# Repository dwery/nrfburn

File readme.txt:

This hardware/software package allows full access to the flash area of the Nordic nRF24LU1+ and nRF24LE1 microcontrollers.

The programmer is based on an Atmel ATmega AVR which handles the SPI communication and access to the flash area of the Nordic nRF MCUs. It can erase, write and read the MainBlock and InfoBlock of the nRF flash.

NOTE: Flash read access is only possible if it has been allowed by the nRF InfoPage configuration.

nrfburn can be used to access the flash of "bricked" nRF24LU1+ (both versions: F16 and F32) or nRF24LE1 MCUs. You can reprogram the bootloader or write any other HEX file into the flash area.

Tha programmer hardware is built around an Atmel ATmega88p microcontroller, but ATmega168p or ATmega328p can be used as well. The programmer firmware uses V-USB for communication with the PC. The PCB has breakout footprints compatibile with the SparkFun nRF24LU1+ breakout board, and a generic nRF24LU1+ dongle. This means that you can just plug these breakouts into the programmer to flash the nRF MCU.

Project modules:

AVR circut - Eagle CAD files for the AVR programmer circuit.

firmware - The AVR programmer firmware. It parses requests received from USB and executes SPI commands to access the nRF flash.

nrfburn - PC software which sends commands to the AVR programmer. Written in C++, it is cross-platform and can be compiled with gcc for Linux or Windows (MinGW).

nrfburn is still under active development, and parts of it are not working. It has not yet been tested with nRF24LE1 and problems are expected.

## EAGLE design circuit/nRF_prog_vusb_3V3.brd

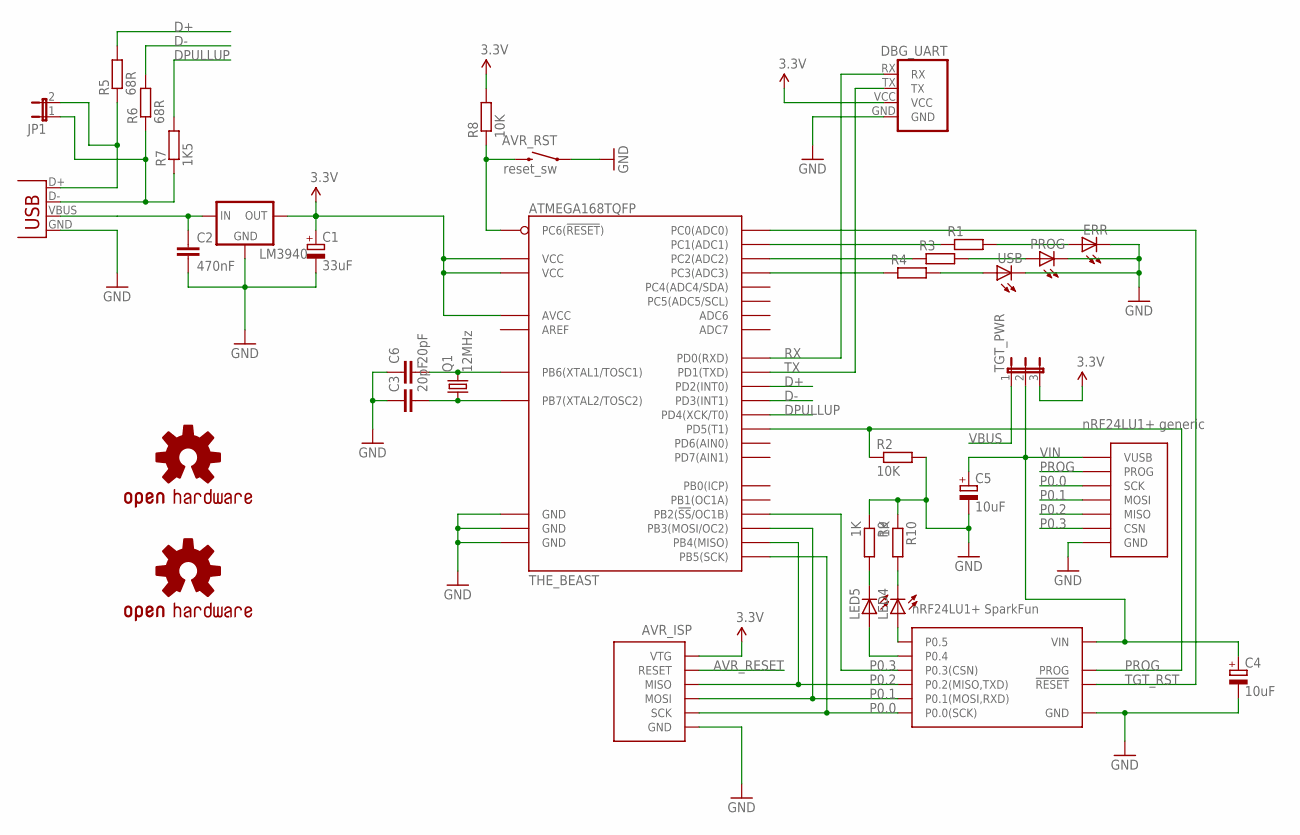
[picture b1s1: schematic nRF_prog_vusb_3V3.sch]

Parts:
AVR_ISP: AVR-ISP-6SMALL_FP; AVR-ISP-6-SMALL-FP
AVR_RST: reset_sw; TACTILE_SWITCH_SMD
C1: 33uF; SMC_B
C2: 470nF; C0805K
C3, C6: 20pF; C0805
C4, C5: 10uF; SMC_B
DBG_UART: UART_PORT
ERR: LEDCHIPLED_0805; CHIPLED_0805
JP1: JP1E; JP1
LED4, LED5: LEDCHIPLED_0805; CHIPLED_0805
LM3940: LM3940; SOT223
LU1+_GENERIC: NRF24LU1P_GENERIC
LU1+_SPARKFUN: NRF24LU1P_SPARKFUN_BREAKOUT; NRF24LU+_SPARKFUN_BREAKOUT
PROG: LEDCHIPLED_0805; CHIPLED_0805
Q1: 12MHz; QUARTZ
R1, R3, R4: R-EU_M0805; M0805
R2, R8: 10K; M0805
R5, R6: 68R; M0805
R7: 1K5; M0805
R9, R10: 1K; M0805
TGT_PWR: JP2E; JP2
THE_BEAST: ATMEGA168TQFP; TQFP32-08
U$1: OSHW-LOGOM; OSHW-LOGO-M
U$2: OSHW-LOGOL; OSHW-LOGO-L
USB: LEDCHIPLED_0805; CHIPLED_0805
USB-B: USBPTH; USB-B-PTH

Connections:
3.3V: AVR_ISP.VCC (VTG), C1.+, DBG_UART.VCC, LM3940.3 (OUT), R8.2, TGT_PWR.3, THE_BEAST.4 (VCC), THE_BEAST.6 (VCC), THE_BEAST.18 (AVCC)
AVR_RESET: AVR_ISP.RESET, AVR_RST.3 (2), R8.1, THE_BEAST.29 (PC6(!RESET!))
D+: R5.2, THE_BEAST.32 (PD2(INT0))
D-: R6.2, THE_BEAST.1 (PD3(INT1))
DPULLUP: R7.2, THE_BEAST.2 (PD4(XCK/T0))
GND: AVR_ISP.GND, AVR_RST.1, C1.-, C2.2, C3.1, C4.-, C5.-, C6.1, DBG_UART.GND, ERR.C, LM3940.2 (GND), LM3940.4 (GND), LU1+_GENERIC.GND, LU1+_SPARKFUN.GND, PROG.C, R2.2, R9.1, R10.1, THE_BEAST.3 (GND), THE_BEAST.5 (GND), THE_BEAST.21 (GND), USB.C, USB-B.GND
unnamed: LED4.A, LU1+_SPARKFUN.P0.5
unnamed: LED5.A, LU1+_SPARKFUN.P0.4
unnamed: LED4.C, R10.2
unnamed: LED5.C, R9.2
unnamed: R4.1, THE_BEAST.26 (PC3(ADC3))
unnamed: R3.1, THE_BEAST.25 (PC2(ADC2))
unnamed: R1.1, THE_BEAST.24 (PC1(ADC1))
unnamed: R4.2, USB.A
unnamed: PROG.A, R3.2
unnamed: ERR.A, R1.2
unnamed: C6.2, Q1.2, THE_BEAST.7 (PB6(XTAL1/TOSC1))
unnamed: C3.2, Q1.1, THE_BEAST.8 (PB7(XTAL2/TOSC2))
P0.0: AVR_ISP.SCK, LU1+_GENERIC.SCK, LU1+_SPARKFUN.P0.0 (P0.0(SCK)), THE_BEAST.17 (PB5(SCK))
P0.1: AVR_ISP.MOSI, LU1+_GENERIC.MOSI, LU1+_SPARKFUN.P0.1 (P0.1(MOSI,RXD)), THE_BEAST.15 (PB3(MOSI/OC2))
P0.2: AVR_ISP.MISO, LU1+_GENERIC.MISO, LU1+_SPARKFUN.P0.2 (P0.2(MISO,TXD)), THE_BEAST.16 (PB4(MISO))
P0.3: LU1+_GENERIC.CSN, LU1+_SPARKFUN.P0.3 (P0.3(CSN)), THE_BEAST.14 (PB2(!SS!/OC1B))
PROG: LU1+_GENERIC.PROG, LU1+_SPARKFUN.PROG, R2.1, THE_BEAST.9 (PD5(T1))
RX: DBG_UART.RX, THE_BEAST.30 (PD0(RXD))
TGT_RST: LU1+_SPARKFUN.RESET (!RESET!), THE_BEAST.23 (PC0(ADC0))
TX: DBG_UART.TX, THE_BEAST.31 (PD1(TXD))
USB_D+: JP1.2, R5.1, USB-B.D+
USB_D-: JP1.1, R6.1, R7.1, USB-B.D-
VBUS: C2.1, LM3940.1 (IN), TGT_PWR.1, USB-B.VBUS
VIN: C4.+, C5.+, LU1+_GENERIC.VUSB, LU1+_SPARKFUN.VIN, TGT_PWR.2

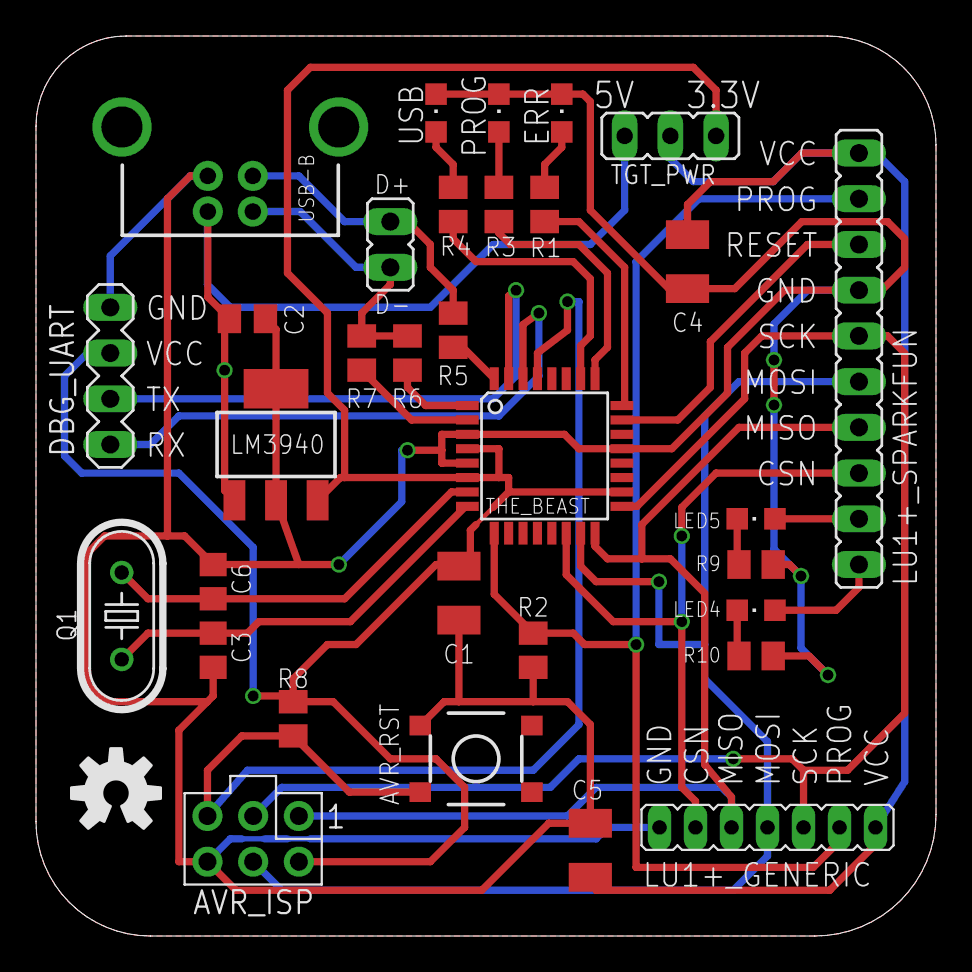
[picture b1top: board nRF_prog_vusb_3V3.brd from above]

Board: 2 copper layers, 50.0 x 50.0 mm, 34 parts (1 on the bottom side), 30 nets.

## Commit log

2013-12-23 added flash verification
2013-12-23 linux usb_dev_handle casts
2013-12-23 labels and messages fix
2013-12-29 New version works uses reset which hopefully fixes the problems with programming nRF24LU1+ It looks like it is necessary to reset the target before and/or after programming.
2014-01-20 read InfoPage now works correctly
2014-02-03 added testpins for USB
2014-02-08 Optimized USB programmer protocol. Now it does not send blocks full of of 0xff bytes hence saving bandwidth.
2014-02-08 Added precompiled LU1+ bootloader HEX files. Fixed writing to flash.
2014-02-09 USB Keyboard example enumerates
2014-02-15 add ignoreCheck parameter to VerifyMainBlock
2014-02-15 now empty packages are NAKed when there's nothing to send
2014-02-27 cleaned up some of the examples
2014-02-27 strcmpi -> strcasecmp
2014-03-04 added circuit schematic in PDF
2014-03-13 added BootloaderHID for the programmer
2014-03-14 small improvements in the bootloader
2014-03-16 added bootloader support for host program
2014-03-16 Cleaned up the LED references. USB configuration LED is now working.
2014-04-22 fixed bootloader
2014-10-20 fixed flash size warning
2015-01-26 start of support for using USBasp as a programmer
2015-02-10 static linking of C / C++ libraries for nrfburn.exe
2015-12-06 Migrating wiki contents from Google Code

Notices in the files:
parts and their libraries:
SparkFun: Licensing: CC v3.0 Share-Alike You are welcome to use this library for commercial purposes.
